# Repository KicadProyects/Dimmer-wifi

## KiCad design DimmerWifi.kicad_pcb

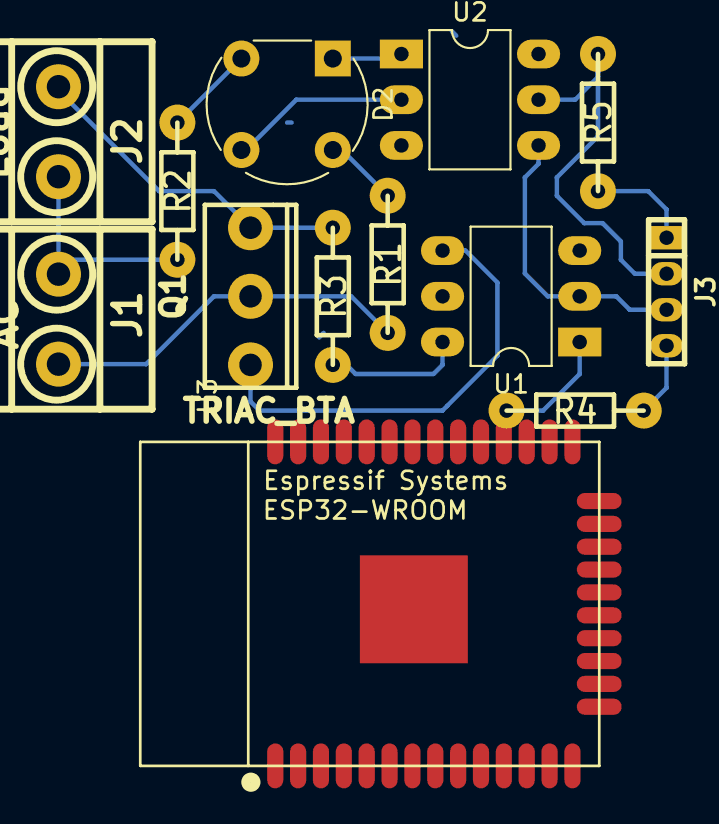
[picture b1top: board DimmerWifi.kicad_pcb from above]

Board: 2 copper layers, 13 parts (0 on the bottom side), 14 nets.

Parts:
D2: D_Bridge_+A-A; Diode_Bridge_Round_D8.9mm
J1: AC; mkds_1,5-2
J2: Load; mkds_1,5-2
J3: Conn_01x04; pin_strip_2mm_4
Q1: TRIAC_BTA; to220
R1, R2: 30k; RC03
R3: 1k; RC03
R4: 180; RC03
R5: 3.3k; RC03
U1: MOC3021M; DIP-6_W7.62mm_LongPads
U2: 4N25; DIP-6_W7.62mm_LongPads
U3: ESP32-WROOM

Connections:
+3.3V: J3.1, R5.1, U3.2
/Fase: J1.2, Q1.2, R1.2
/Neutro: J1.1, J2.2, R2.2
GND: J3.3, U1.2, U2.4, U3.1
unnamed: D2.1, U2.1
unnamed: D2.2, R2.1
unnamed: D2.3, U2.2
unnamed: D2.4, R1.1
unnamed: J2.1, Q1.3, R3.1
unnamed: J3.2, R5.2, U2.5
unnamed: J3.4, R4.2
unnamed: Q1.1, U1.4
unnamed: R3.2, U1.6
unnamed: R4.1, U1.1

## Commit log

2017-10-30 :neckbeard: Added .gitattributes & .gitignore files
2017-11-01 add esp32
